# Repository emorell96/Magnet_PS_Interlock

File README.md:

# Magnet_PS_Interlock
 Interlock PCB design for the magnet interlock

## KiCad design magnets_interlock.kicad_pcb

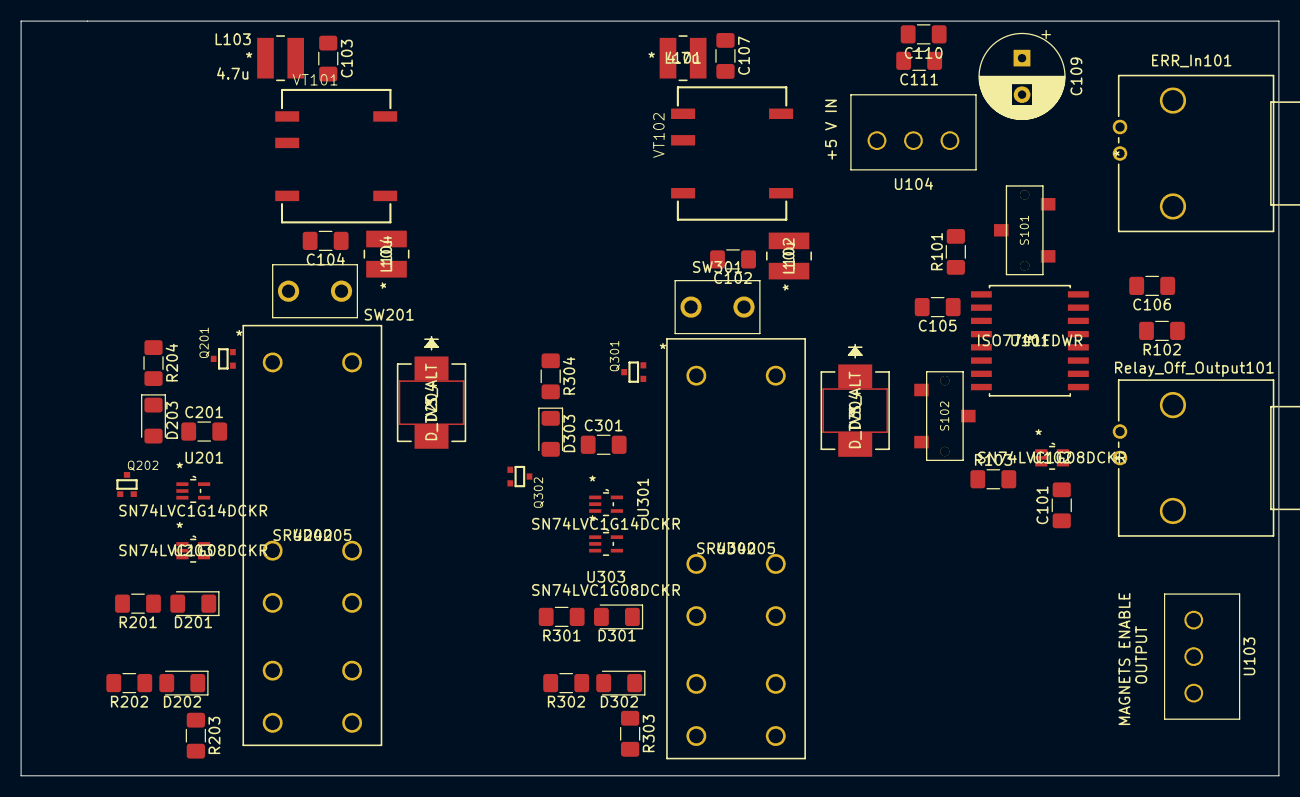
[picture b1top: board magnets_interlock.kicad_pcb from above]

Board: 2 copper layers, 120.7 x 72.4 mm, 57 parts (0 on the bottom side), 38 nets, no tracks yet.

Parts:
C101, C105, C106, C201, C301: 0.1u; C_1206_3216Metric_Pad1.42x1.75mm_HandSolder
C102, C104: 2.2u; C_1206_3216Metric_Pad1.42x1.75mm_HandSolder
C103, C107, C110, C111: 4.7u; C_1206_3216Metric_Pad1.42x1.75mm_HandSolder
C109: 47u; CP_Radial_D8.0mm_P3.50mm
D201, D203, D301, D303: LTST-C150KRKT; LED_1206_3216Metric_Pad1.42x1.75mm_HandSolder
D202, D302: LTST-C150KGKT; LED_1206_3216Metric_Pad1.42x1.75mm_HandSolder
D204, D304: D_TVS_ALT; SM15T15CA
ERR_In101: BNC_Input_female; 1-1337543-0
L101, L103: 4.7u; VLCF4024T-4R7N1R4-2
L102, L104: 10u; VLCF4024T-4R7N1R4-2
Q201, Q202, Q301, Q302: BSS138W; SOT323-R
R101, R102, R103: 10k; R_1206_3216Metric_Pad1.42x1.75mm_HandSolder
R201, R202, R204, R301, R302, R304: 1k; R_1206_3216Metric_Pad1.42x1.75mm_HandSolder
R203, R303: 100k; R_1206_3216Metric_Pad1.42x1.75mm_HandSolder
Relay_Off_Output101: BNC_Input_female; 1-1337543-0
S101, S102: CL-SB-12B-01T; CL-SB-12B
SW201, SW301: SW_Push; TP11SH8CQE
U101: ISO7741FDWR
U102, U203, U303: SN74LVC1G08DCKR; SN74LVC1G14DCKR
U103, U104: 691321100003
U201, U301: SN74LVC1G14DCKR
U202, U302: SR4D4005
VT101, VT102: NXJ1S0505MC-R7; VREG_NXJ1S0505MC-R7

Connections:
+5VIN: C103.1, C105.1, C107.1, C109.1, C110.2, C111.2, L101.2, L103.2, S102.1, U101.1, U104.1
+5VOut1: C102.1, C106.2, C301.2, L102.1, R304.1, SW301.1, U101.16, U301.5, U302.21, U302.43, U303.5
+5VOut2: C101.2, C104.1, C201.2, L104.1, R204.1, S101.1, SW201.1, U102.5, U201.5, U202.21, U202.43, U203.5
/Relay_1/Enable_Conn_1: U103.3, U302.34
/Relay_1/ErrSig1: Q301.1, U101.14, U301.2
/Relay_1/Relay-Off-Sig: D302.1, D304.1, R303.1, SW301.2, U102.1, U302.44, U302.A1, U303.1
/Relay_2/Enable_Conn_1: U202.34, U302.33
/Relay_2/Enable_Conn_2: U103.2, U202.33
/Relay_2/ErrSig1: Q201.1, U101.13, U201.2
/Relay_2/Relay-Off-Sig: D202.1, D204.1, R203.1, SW201.2, U102.2, U202.44, U202.A1, U203.1
GND: C101.1, C102.2, C104.2, C106.1, C201.1, C301.1, D204.2, D304.2, Q201.2, Q202.2, Q301.2, Q302.2, R101.1, R102.1, R201.2, R202.2, R203.2, R301.2, R302.2, R303.2, S101.3, U101.9, U101.15, U102.3, U201.3, U203.3, U301.3, U303.3, VT101.7, VT102.7
unnamed: D201.1, U202.22
unnamed: D201.2, R201.1
unnamed: D202.2, R202.1
unnamed: D203.1, R204.2
unnamed: D203.2, Q202.3
unnamed: D301.1, U302.22
unnamed: D301.2, R301.1
unnamed: D302.2, R302.1
unnamed: D303.1, R304.2
unnamed: D303.2, Q302.3
unnamed: ERR_In101.1, U101.3, U101.4
unnamed: L101.1, VT102.3
unnamed: L102.2, VT102.8
unnamed: L103.1, VT101.3
unnamed: L104.2, VT101.8
unnamed: Q201.3, U202.A2
unnamed: Q202.1, U203.4
unnamed: Q301.3, U302.A2
unnamed: Q302.1, U303.4
unnamed: R101.2, S101.2, U101.10
unnamed: R102.2, U101.12
unnamed: R103.2, S102.2, U101.7
unnamed: Relay_Off_Output101.1, U101.6
unnamed: U201.4, U203.2
unnamed: U301.4, U303.2
PWR_GND_IN: C103.2, C105.2, C107.2, C109.2, C110.1, C111.1, ERR_In101.2, ERR_In101.3, ERR_In101.4, R103.1, Relay_Off_Output101.2, Relay_Off_Output101.3, Relay_Off_Output101.4, S102.3, U101.2, U101.5, U101.8, U104.3, VT101.1, VT102.1
Relay_off_signal: U101.11, U102.4

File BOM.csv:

"Id";"Designator";"Package";"Quantity";"Designation";"Supplier and ref";
1;"U104,U103";"691321100003";2;"691321100003";;;
2;"Q201,Q202,Q301,Q302";"SOT323-R";4;"BSS138W";;;
3;"U201,U301";"SN74LVC1G14DCKR";2;"SN74LVC1G14DCKR";;;
4;"U203,U303,U102";"SN74LVC1G14DCKR";3;"SN74LVC1G08DCKR";;;
5;"S102,S101";"CL-SB-12B";2;"CL-SB-12B-01T";;;
6;"U101";"ISO7741FDWR";1;"ISO7741FDWR";;;
7;"D204,D304";"SM15T15CA";2;"D_TVS_ALT";;;
8;"ERR_In101,Relay_Off_Output101";"1-1337543-0";2;"BNC_Input_female";;;
9;"SW201,SW301";"TP11SH8CQE";2;"SW_Push";;;
10;"C105,C106,C201,C301,C101";"C_1206_3216Metric_Pad1.42x1.75mm_HandSolder";5;"0.1u";;;
11;"C107,C110,C111,C103";"C_1206_3216Metric_Pad1.42x1.75mm_HandSolder";4;"4.7u";;;
12;"D201,D203,D301,D303";"LED_1206_3216Metric_Pad1.42x1.75mm_HandSolder";4;"LTST-C150KRKT";;;
13;"D202,D302";"LED_1206_3216Metric_Pad1.42x1.75mm_HandSolder";2;"LTST-C150KGKT";;;
14;"R101,R102,R103";"R_1206_3216Metric_Pad1.42x1.75mm_HandSolder";3;"10k";;;
15;"R201,R202,R204,R301,R302,R304";"R_1206_3216Metric_Pad1.42x1.75mm_HandSolder";6;"1k";;;
16;"R203,R303";"R_1206_3216Metric_Pad1.42x1.75mm_HandSolder";2;"100k";;;
17;"U202,U302";"SR4D4005";2;"SR4D4005";;;
18;"VT102,VT101";"VREG_NXJ1S0505MC-R7";2;"NXJ1S0505MC-R7";;;
19;"C109";"CP_Radial_D8.0mm_P3.50mm";1;"47u";;;
20;"C102,C104";"C_1206_3216Metric_Pad1.42x1.75mm_HandSolder";2;"2.2u";;;
21;"L101,L103";"VLCF4024T-4R7N1R4-2";2;"4.7u";;;
22;"L102,L104";"VLCF4024T-4R7N1R4-2";2;"10u";;;

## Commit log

2020-06-25 KiCAD Project File Added
2020-06-25 File Restructure
2020-06-25 Adding DigiKey Library To Project
    I think this is adding the DigiKey Library to my local project. I'm not entirely sure however if this will allow you to download it when you clone the repo
2020-06-25 Adding Isolation to Power and Signal Inputs
2020-06-25 Buffered Ouptut of Isolator. Created sub-sheet for relays
2020-06-26 New Power and Signal Isolation
    Making 5V standard and using Enrique parts
2020-06-27 Adding 5V components
2020-06-27 Saving a few things
    Before I get rid of the +24 Volt stuff
2020-06-29 Rough Draft of Relay Circuit
2020-06-29 Made 5V local label to each sheet
2020-06-29 Annotations
2020-06-29 Bypass everything and run Error Check
2020-06-29 Adding Footprints
2020-06-29 All Footprints assembled!
2020-06-29 Good Initial Layout
2020-06-30 Enrique changes
2020-06-30 Draft 1 Almost There
2020-07-01 Next Draft

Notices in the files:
parts and their libraries:
Copyright 2016 Accelerated Designs. All rights reserved.
